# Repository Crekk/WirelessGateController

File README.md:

# Wireless Gate Controller

> **Note on authorship:** Large parts of the firmware source code and this initial (placeholder) README were generated with the use of AI. The README has not yet been fully reviewed or verified by me. All hardware design, including the schematic and PCB layout, was done entirely by me.

An ESP32-based Wi-Fi controller for garage doors and gates, featuring a custom PCB, three relay outputs, MQTT communication, and native Home Assistant MQTT discovery.

The controller is designed to retrofit an existing gate automation system by emulating its **Up**, **Stop**, and **Down** push buttons, rather than replacing the motor controller itself.

**Hardware:** revision 1.0 · **Firmware:** version 1.0.2 · **Status:** manufactured prototype, hardware validation pending

## Features

- Three independently controlled, normally open relay outputs with nominal 500 ms pulses.
- Wi-Fi and MQTT integration with Home Assistant automatic device and button discovery.
- MQTT availability reporting, periodic diagnostics and on-demand status requests.
- Automatic Wi-Fi and MQTT reconnection, with recovery reboots after prolonged connectivity failures.
- Periodic gateway reachability checks.
- Password-protected web interface for over-the-air (OTA) firmware updates.
- Static IPv4 configuration and local mDNS hostname.
- Custom two-layer, through-hole PCB designed in KiCad and manufactured by PCBWay.
- Automated firmware compilation with GitHub Actions.

## System overview

```mermaid
flowchart LR
    HA[Home Assistant] <-->|MQTT| Broker[MQTT broker]
    Broker <-->|Wi-Fi / MQTT| ESP[ESP32 DevKit V1]
    ESP --> Drivers[Transistor drivers]
    Drivers --> Relays[3 relay contacts]
    Relays --> Gate[Existing gate controller]
    Browser[Web browser] -->|HTTP OTA| ESP
```

Home Assistant sends commands to the ESP32 through an MQTT broker. The ESP32 briefly energizes the corresponding relay, closing its normally open contacts to emulate a button press. The existing gate controller remains responsible for motor operation, travel limits, and safety functions.

## Hardware

| Top view | Bottom view |
| :---: | :---: |
|  |  |

### Specifications

| Parameter | Specification |
| --- | --- |
| PCB revision | 1.0 |
| PCB dimensions | 93.25 × 73 mm |
| PCB layers | 2 |
| Microcontroller | ESP32 DevKit V1 (30-pin module) |
| Power input | Regulated 5 V DC, screw terminal or barrel jack |
| Relays | 3 × Hongfa JQC-3FF-005-1Z, 5 V SPDT |
| Relay drivers | 3 × BC337 NPN transistors, active HIGH |
| Flyback protection | 3 × 1N5819 Schottky diodes |
| Relay outputs | Normally open, potential-free contacts |
| Terminal pitch | 5.00 mm |
| Assembly | Through-hole components |
| Wireless interface | 2.4 GHz Wi-Fi |
| Design software | KiCad 10 (current project format) |
| PCB manufacturer | PCBWay |

### Relay mapping

| Function | ESP32 GPIO | Relay | Output connector | MQTT command topic |
| --- | ---: | --- | --- | --- |
| Up | 27 | K1 | J1 | `garage/relay1` |
| Stop | 26 | K2 | J2 | `garage/relay2` |
| Down | 25 | K3 | J3 | `garage/relay3` |

Each relay is driven by an active-HIGH transistor circuit. The firmware energizes the selected relay for a nominal 500 ms and releases it automatically. All three outputs are initialized to their inactive state during firmware setup.

### Additional connectors

| Reference | Purpose |
| --- | --- |
| J4 | Photocell connection (hardware provision) |
| J5 | 5 V DC power input |
| J6 | Antenna data connection |
| J7 | Antenna 5 V supply |
| J8 | DC barrel jack |
| U2 | Six-pin expansion header |
| TP1 / TP2 | 5 V / GND test points |

The photocell and antenna connections are hardware provisions; the current firmware does not implement their functionality.

### Design files and manufacturing

- [KiCad project](hardware/WirelessGateController.kicad_pro)
- [PCB layout](hardware/WirelessGateController.kicad_pcb)
- [Schematic source](hardware/WirelessGateController.kicad_sch)
- [Schematic PDF](docs/schematic.pdf)
- [Original PCBWay manufacturing archive](manufacturing/v1.0/PCBWay.zip)
- [Bill of materials](manufacturing/v1.0/files/PCBWay_bom.csv)
- [Extracted Gerbers, drill files, placement data and netlist](manufacturing/v1.0/files/)

Custom KiCad symbols, footprints and the ESP32 STEP model are included under `hardware/libraries/`. Install the standard KiCad 10 libraries and 3D models to display the complete project.

The PCB renders use visually similar standard KiCad models for the relays and screw terminals where the original component models are unavailable. These substitutions affect visualization only, not the PCB footprints or bill of materials.

The manufacturing archive preserves the original files submitted for revision 1.0 production. It is not a regenerated export of the current KiCad project.

## Firmware

The firmware is written in C++ using the Arduino framework and built with PlatformIO.

| Dependency | Version |
| --- | --- |
| PlatformIO Core (CI) | 6.2.0 |
| Espressif32 platform | 8.0.0 |
| Arduino ESP32 core (verified build) | 3.3.12 |
| PubSubClient | 2.8.0 |
| PlatformIO board | `esp32dev` |

### Build and flash

Install [PlatformIO Core](https://docs.platformio.org/en/latest/core/installation/index.html) or the PlatformIO IDE extension for Visual Studio Code.

Clone the repository and prepare your local configuration:

```sh
git clone https://github.com/Crekk/WirelessGateController.git
cd WirelessGateController/firmware
cp include/secrets.example.h include/secrets.h
```

Edit `include/secrets.h` and configure:

- Wi-Fi SSID and password.
- Static IP address, subnet, gateway and DNS server.
- MQTT broker address, port and credentials.
- OTA web interface username and password.

The example configuration is provided in [secrets.example.h](firmware/include/secrets.example.h). Your actual `secrets.h` is excluded from version control.

Build the firmware:

```sh
pio run
```

Connect the ESP32 via USB and upload:

```sh
pio run -t upload
```

Monitor serial output at 115200 baud:

```sh
pio device monitor
```

The firmware binary is generated at `.pio/build/esp32dev/firmware.bin` within the `firmware/` directory.

### Home Assistant integration

With Home Assistant's MQTT integration and the controller configured to use the same broker, the firmware publishes discovery configurations for a device named **Garage Controller** with three button entities:

- Up
- Stop
- Down

The discovery messages are retained by the broker, while button commands are sent without the retain flag. The device reports its availability using an MQTT Last Will and Testament message.

No custom Home Assistant component is required. The discovery behavior has been implemented in firmware; integration testing on the custom PCB is still pending.

### MQTT interface

| Topic | Direction | Purpose |
| --- | --- | --- |
| `garage/relay1` | Subscribe | Pulse Up relay |
| `garage/relay2` | Subscribe | Pulse Stop relay |
| `garage/relay3` | Subscribe | Pulse Down relay |
| `garage/status` | Subscribe | Request diagnostics |
| `garage/state` | Publish | Most recent controller event (retained) |
| `garage/availability` | Publish | `online` or `offline` (retained) |
| `garage/info` | Publish | Diagnostic information (not retained) |

Home Assistant uses the payload `PRESS` for its button commands. The firmware currently triggers commands based on the topic, regardless of payload contents. **Do not retain relay command messages.**

Diagnostic messages are published on connection, on request, and approximately once per minute. They include the device name, Wi-Fi status, IP address, gateway reachability, RSSI, uptime, and relay activity flags.

The state topic reports controller events rather than the physical position of the gate. The firmware does not currently implement gate position feedback or a Home Assistant cover entity.

### Over-the-air updates

After the initial USB flash, the firmware can be updated through its local web interface:

```text
http://garage-esp32.local/
```

If mDNS is unavailable, use the configured static IP address instead. Authenticate using the OTA credentials, select the newly compiled `firmware.bin`, and upload it. The controller reboots after a successful update.

The MQTT connection and OTA web interface currently use unencrypted TCP/HTTP. They are intended for a trusted local network, not direct exposure to the internet.

### Connectivity recovery

| Condition | Check / retry interval | Recovery reboot threshold |
| --- | --- | --- |
| Wi-Fi disconnected | 5 seconds | 3 minutes |
| MQTT disconnected | 5 seconds | 5 minutes |
| Gateway unreachable | 10 seconds | 60 seconds |

Gateway checks use a TCP connection to port 53 on the configured gateway. The current implementation therefore assumes that the gateway accepts TCP DNS connections.

## Continuous integration

The [Firmware Build workflow](.github/workflows/firmware.yml) runs on GitHub Actions whenever firmware files or the workflow itself change, on qualifying pushes and pull requests. It can also be started manually.

The workflow creates a clean Ubuntu build environment, installs a pinned PlatformIO version, copies the example credentials file, and compiles the firmware without requiring any private configuration.

The first CI build completed successfully on 26 November 2026:

| Resource | Usage |
| --- | ---: |
| RAM | 50,120 / 327,680 bytes (15.3%) |
| Application flash partition | 973,456 / 1,310,720 bytes (74.3%) |

CI verifies compilation only. It does not validate network behavior, relay operation, or the assembled hardware.

## Repository structure

```text
WirelessGateController/
├── .github/workflows/       # Automated firmware build
├── docs/                    # Schematic PDF and PCB renders
│   └── images/
├── firmware/                # PlatformIO firmware project
│   ├── include/             # Example configuration
│   ├── src/                 # C++ firmware
│   └── platformio.ini
├── hardware/                # KiCad schematic and PCB project
│   └── libraries/          # Custom symbols, footprints and 3D model
└── manufacturing/v1.0/      # Original PCBWay production package
```

## Project status

- [x] Revision 1.0 schematic and PCB design
- [x] PCB fabrication by PCBWay
- [x] KiCad project and custom library restoration
- [x] Firmware review and local compilation
- [x] GitHub Actions clean-environment build
- [x] Schematic, manufacturing files and PCB renders archived
- [ ] Electrical bench testing of the assembled custom PCB
- [ ] Verify relay operation, MQTT discovery and OTA updates on the target hardware
- [ ] Resolve outstanding schematic ERC findings and review PCB DRC warnings
- [ ] Photograph the physical hardware and finalize release documentation

Revision 1.0 is a manufactured prototype, not a fully validated product. The relays are intended to emulate the low-voltage control inputs of an existing gate controller, not to switch the gate motor or mains power. Direction interlocking and gate safety functions remain the responsibility of the existing gate controller.

## License and acknowledgements

The original firmware, hardware design and documentation are licensed under
the [MIT License](LICENSE).

Third-party component libraries, 3D models and Madoka Magica artwork are
excluded from this license and remain subject to their respective copyright
and licensing terms.

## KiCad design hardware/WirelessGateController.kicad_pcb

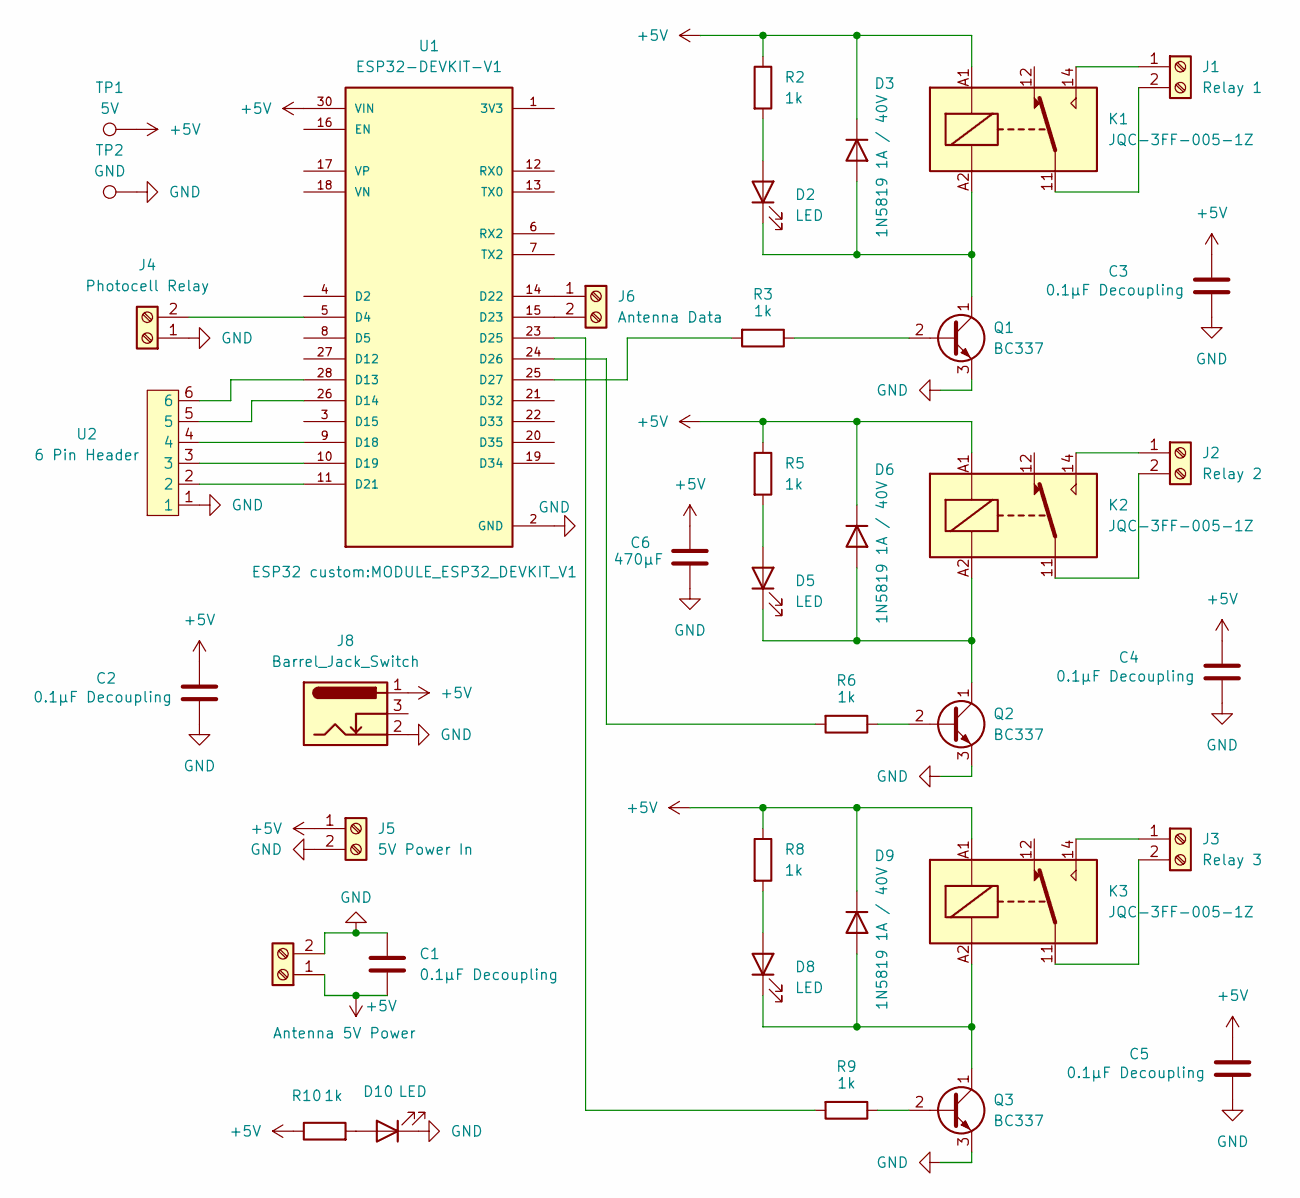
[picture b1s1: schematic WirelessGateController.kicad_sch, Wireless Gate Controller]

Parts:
C1, C2, C3, C4, C5: 0.1µF Decoupling; C_Disc_D3.8mm_W2.6mm_P2.50mm
C6: 470µF; C_Radial_D8.0mm_H11.5mm_P3.50mm
D2, D5, D8, D10: LED; LED_D1.8mm_W3.3mm_H2.4mm
D3, D6, D9: 1N5819 1A / 40V; D_A-405_P7.62mm_Horizontal
J1: Relay 1; TerminalBlock_MaiXu_MX126-5.0-02P_1x02_P5.00mm
J2: Relay 2; TerminalBlock_MaiXu_MX126-5.0-02P_1x02_P5.00mm
J3: Relay 3; TerminalBlock_MaiXu_MX126-5.0-02P_1x02_P5.00mm
J4: Photocell Relay; TerminalBlock_MaiXu_MX126-5.0-02P_1x02_P5.00mm
J5: 5V Power In; TerminalBlock_MaiXu_MX126-5.0-02P_1x02_P5.00mm
J6: Antenna Data; TerminalBlock_MaiXu_MX126-5.0-02P_1x02_P5.00mm
J7: Antenna 5V Power; TerminalBlock_MaiXu_MX126-5.0-02P_1x02_P5.00mm
J8: Barrel_Jack_Switch; BarrelJack_Horizontal
K1, K2, K3: JQC-3FF-005-1Z; Relay_SPDT_Hongfa_JQC-3FF_0XX-1Z
Q1, Q2, Q3: BC337; TO-92_Inline
R2, R3, R5, R6, R8, R9, R10: 1k; R_Axial_DIN0207_L6.3mm_D2.5mm_P7.62mm_Horizontal
TP1: 5V; TestPoint_Pad_2.0x2.0mm
TP2: GND; TestPoint_Pad_2.0x2.0mm
U1: ESP32-DEVKIT-V1; MODULE_ESP32_DEVKIT_V1; PARTREV N/A
U2: 6 Pin Header; PinHeader_1x06_P2.54mm_Vertical

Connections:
+5V: C1.2, C2.1, C3.1, C4.1, C5.1, C6.1, D3.1 (K), D6.1 (K), D9.1 (K), J5.1, J7.1, J8.1, K1.A1, K2.A1, K3.A1, R2.1, R5.1, R8.1, R10.1, TP1.1, U1.30 (VIN)
GND: C1.1, C2.2, C3.2, C4.2, C5.2, C6.2, D10.1 (K), J4.1, J5.2, J7.2, J8.2, Q1.3 (E), Q2.3 (E), Q3.3 (E), TP2.1, U1.2 (GND), U1.29 (GND), U2.1
unnamed: D2.2 (A), R2.2
unnamed: D2.1 (K), D3.2 (A), K1.A2, Q1.1 (C)
unnamed: D5.2 (A), R5.2
unnamed: D5.1 (K), D6.2 (A), K2.A2, Q2.1 (C)
unnamed: D8.2 (A), R8.2
unnamed: D8.1 (K), D9.2 (A), K3.A2, Q3.1 (C)
unnamed: D10.2 (A), R10.2
unnamed: J1.1, K1.14
unnamed: J1.2, K1.11
unnamed: J2.1, K2.14
unnamed: J2.2, K2.11
unnamed: J3.1, K3.14
unnamed: J3.2, K3.11
unnamed: J4.2, U1.5 (D4)
unnamed: J6.1, U1.14 (D22)
unnamed: J6.2, U1.15 (D23)
unnamed: Q1.2 (B), R3.1
unnamed: Q2.2 (B), R6.1
unnamed: Q3.2 (B), R9.1
unnamed: U1.28 (D13), U2.6
unnamed: U1.26 (D14), U2.5
unnamed: U1.9 (D18), U2.4
unnamed: U1.10 (D19), U2.3
unnamed: U1.11 (D21), U2.2
unnamed: R9.2, U1.23 (D25)
unnamed: R6.2, U1.24 (D26)
unnamed: R3.2, U1.25 (D27)

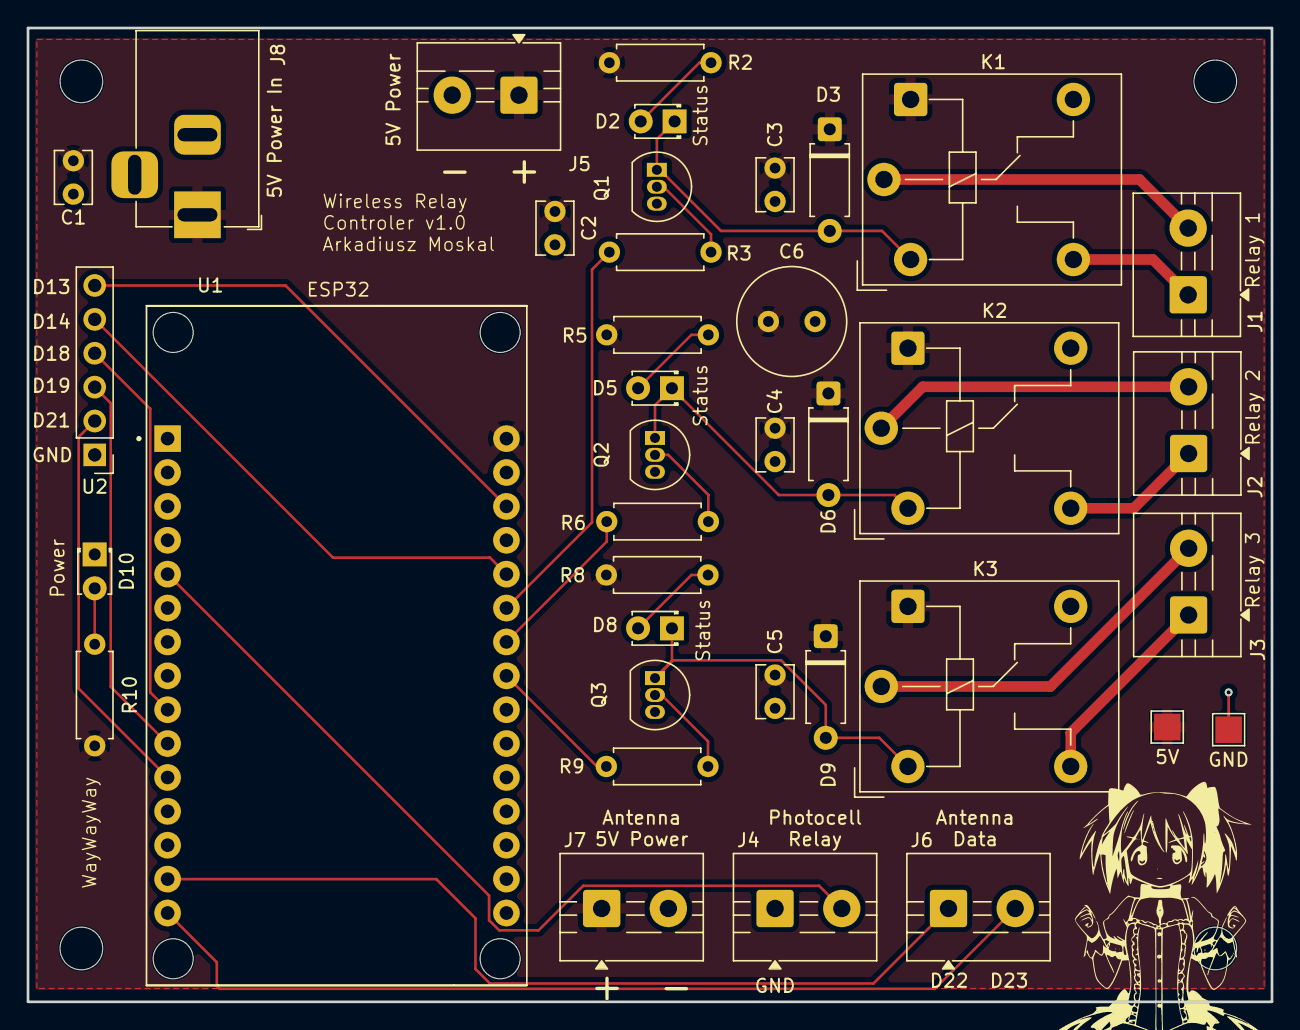
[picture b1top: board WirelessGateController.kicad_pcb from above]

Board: 2 copper layers, 93.2 x 73.0 mm, 38 parts (0 on the bottom side), 29 nets.
